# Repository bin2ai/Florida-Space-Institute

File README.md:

# Florida Space Institute
This repository is used to maintain my work on the software and hardware files for various projects.

<br>`QPACE's WTC PCB Layout`</br>

<br>`QPACE Avionics stack`</br>

<br>`QPACE before Integration`</br>

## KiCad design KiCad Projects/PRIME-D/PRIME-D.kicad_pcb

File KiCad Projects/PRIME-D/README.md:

# Prime-D
This KiCad project includes both the schematic and pcb-layout for FSI drop tower project "Prime-D".  This circuit board should be treated as an Arduino "Shield" and be placed on top of the Arduino Uno socket.

## Usage
This project requires KiCad Version 5.0 and after to use.

## Software
Again please note that this Prime-D circuit board should be treated as an Arduino Uno shield.  Build and flash the Arduion '.ino. file onto the arduino uno board that will be mounted to this Prime-D Arduino Shield. 
<br>You can find the software in the [Arduino/Prime-D/](/KiCad%20Projects/PRIME-D/Arduino/Prime-D/Prime-D.ino) folder.</br>

## Documents Folder
The documents folder contains;
  * [the bill of materials (BOM)](/KiCad%20Projects/PRIME-D/documents/BOM/)
  * [all of the components datasheets](/KiCad%20Projects/PRIME-D/documents/datasheets/)
  * [gerber files](/KiCad%20Projects/PRIME-D/documents/Gerbers/)
  * [pictures](/KiCad%20Projects/PRIME-D/documents/pictures/)
  * [previous revisions](/KiCad%20Projects/PRIME-D/documents/Revisions/)
  * [pdf of both the schematic and pcb layout](/KiCad%20Projects/PRIME-D/documents/schematic_n_PCBlayout/)
  * [Arduino Code](/KiCad%20Projects/PRIME-D/Arduino/Prime-D/Prime-D.ino)

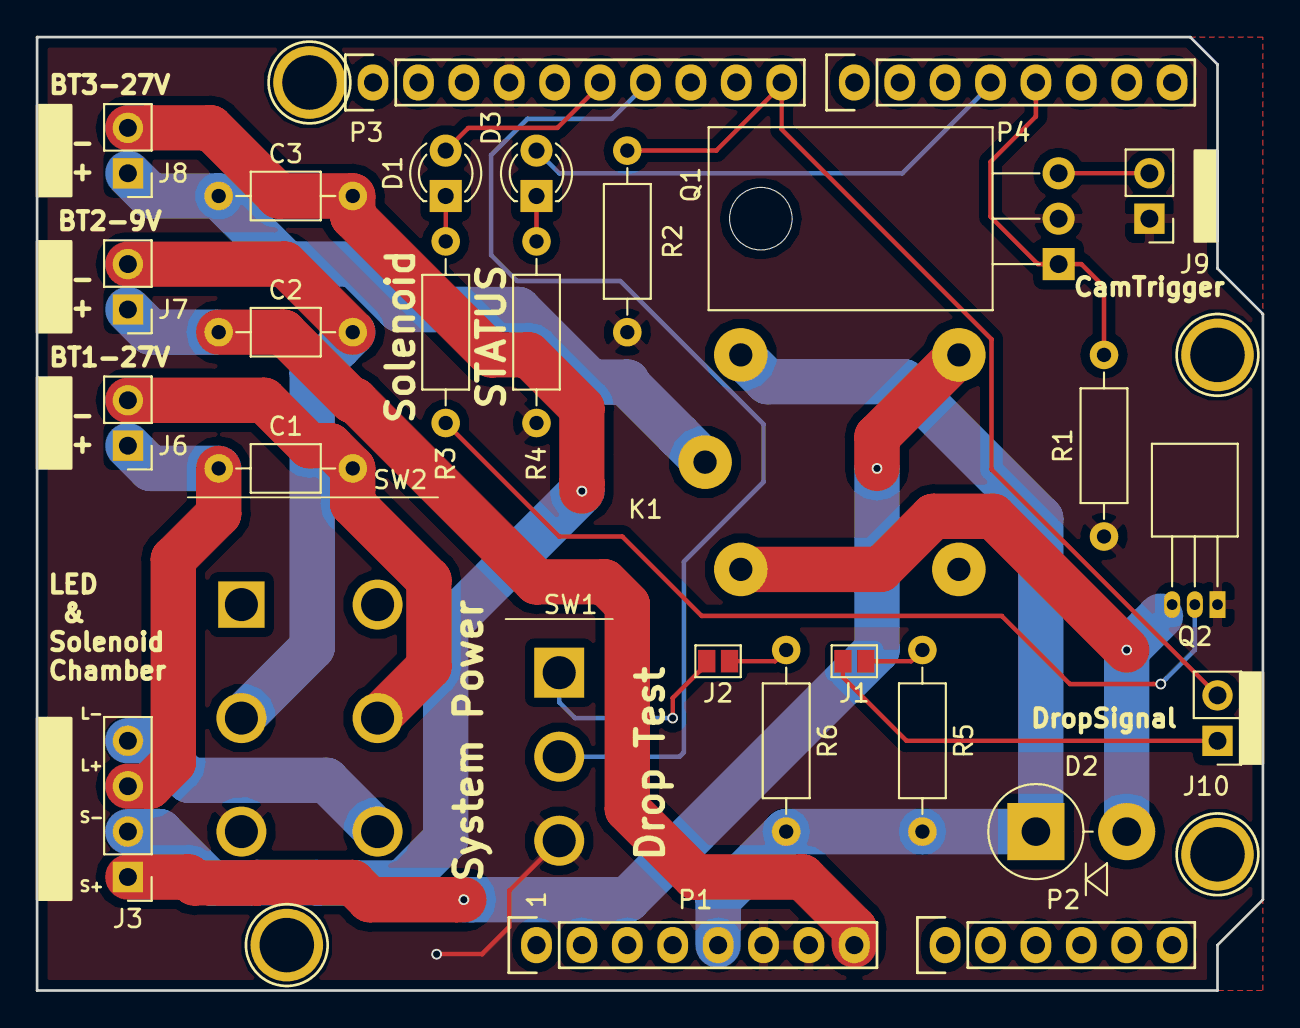
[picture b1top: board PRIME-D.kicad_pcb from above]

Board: 2 copper layers, 68.6 x 53.3 mm, 33 parts (0 on the bottom side), 24 nets.

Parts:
C1, C2, C3: 1uF; C_Axial_L3.8mm_D2.6mm_P7.50mm_Horizontal
D1, D3: LED; LED_D3.0mm
D2: 1N4007; D_DO-201AD_P5.08mm_Vertical_AnodeUp
J1, J2: GS2
J3: Connector_Chamber; PinHeader_1x04_P2.54mm_Vertical
J6: BAT1_27V; PinHeader_1x02_P2.54mm_Vertical
J7: BAT2_9V; PinHeader_1x02_P2.54mm_Vertical
J8: BAT3_27V; PinHeader_1x02_P2.54mm_Vertical
J9: CameraTrigger; PinHeader_1x02_P2.54mm_Vertical
J10: DropSignal; PinHeader_1x02_P2.54mm_Vertical
K1: ORWH-SH-105D1F,000; Relay_SPST_ORWH-SH-105D1F,000
P1: Power; Socket_Strip_Arduino_1x08
P2: Analog; Socket_Strip_Arduino_1x06
P3: Digital; Socket_Strip_Arduino_1x10
P4: Digital; Socket_Strip_Arduino_1x08
P5, P6, P7, P8: CONN_01X01; Arduino_1pin
Q1: IRLI3705N; TO-220-3_Horizontal
Q2: NPN-2N2222; TO-92_Horizontal1_Inline_Narrow_Oval
R1, R2, R5, R6: 100K; R_Axial_DIN0207_L6.3mm_D2.5mm_P10.16mm_Horizontal
R3, R4: 150; R_Axial_DIN0207_L6.3mm_D2.5mm_P10.16mm_Horizontal
SW1: RED-SW_Push_SPDT; SPDT_4.7mm
SW2: SW_DPDT_x2; DPDT_Pitch7-62x6-35mm

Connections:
+5V: D2.1, K1.1, P1.5, R5.2, R6.2
/3(**): P4.5, Q1.1, R1.2
/4: D3.2, P4.4
/8: J10.2, P3.10, R2.2
/11(**/MOSI): P3.7, SW1.2
/12(MISO): D1.2, P3.6
/BT1_V+: C1.1, J3.3, J6.1
/BT1_V-: C1.2, J6.2, SW2.5
/BT2_V+: C2.1, J7.1, P1.8
/BT2_V-: C2.2, J7.2, SW2.2
/BT3_V+: C3.1, J8.1, K1.4
/BT3_V-: C3.2, J3.2, J8.2
/CameraTrigger_Output: J9.2, Q1.3
/DropSignal_High: J1.2, J10.1
/LEDStrip_V-: J3.4, SW2.6
/SOLENOID+: J3.1, K1.3
GND: J9.1, P1.6, P1.7, P3.4, Q1.2, Q2.1, R1.1, R2.1, R4.1, SW1.3, SW2.3
unnamed: D1.1, R3.2
unnamed: D2.2, K1.5, Q2.3
unnamed: D3.1, R4.2
unnamed: J1.1, R5.1
unnamed: J2.1, R6.1
unnamed: J2.2, SW1.1
unnamed: Q2.2, R3.1

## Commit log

2019-02-14 piCamPacketAssembly - initial commit
2019-02-14 Changed file path (added ground and raspberry pi folders)
2019-02-14 RaspberryPi- PiCam Testing Procedure Files
2019-02-14 corrected to .h264 format
2019-02-17 added pictures
2019-02-19 run through picam settings - NOT TESTED
2019-02-26 initial Prime-D KiCad project commit
    This KiCad project includes both the schematic and pcb-layout for FSI drop tower project "Prime-D". The circuit board should be placed on top of an Arduino Uno after fully populated.
2019-02-26 updated readme.nd added pic
2019-02-26 Updated README.md
    added link to document folders
2019-02-26 Updated README.md for Prime D
2019-02-26 initial CDDR KiCad project Commit
2019-02-26 initial ECR KiCad project commit
2019-02-26 initial WTC KiCad project commit
2019-02-26 added pictures of PCB/Layout
2019-02-26 Update README.md
    added WTC PCBLayout picture
2019-02-26 added more pictures for QPACE
2019-03-06 initial commit R1 - fixed relay pinout
    The schematic symbol was incorrect. Easiest solution was to use incorrect schematic symbol and which pins 2 & 3. Should next make both schematic symbol and PCB-layout footprint logically agree with e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
2019-03-06 Prime D - initial commit R1 - fixed relay pinout
    The schematic symbol was incorrect. Easiest solution was to use incorrect schematic symbol and which pins 2 & 3. Should next make both schematic symbol and PCB-layout footprint logically agree with e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
2019-03-19 initial Prime-D Arduino code
    needs to be tested on hardware
